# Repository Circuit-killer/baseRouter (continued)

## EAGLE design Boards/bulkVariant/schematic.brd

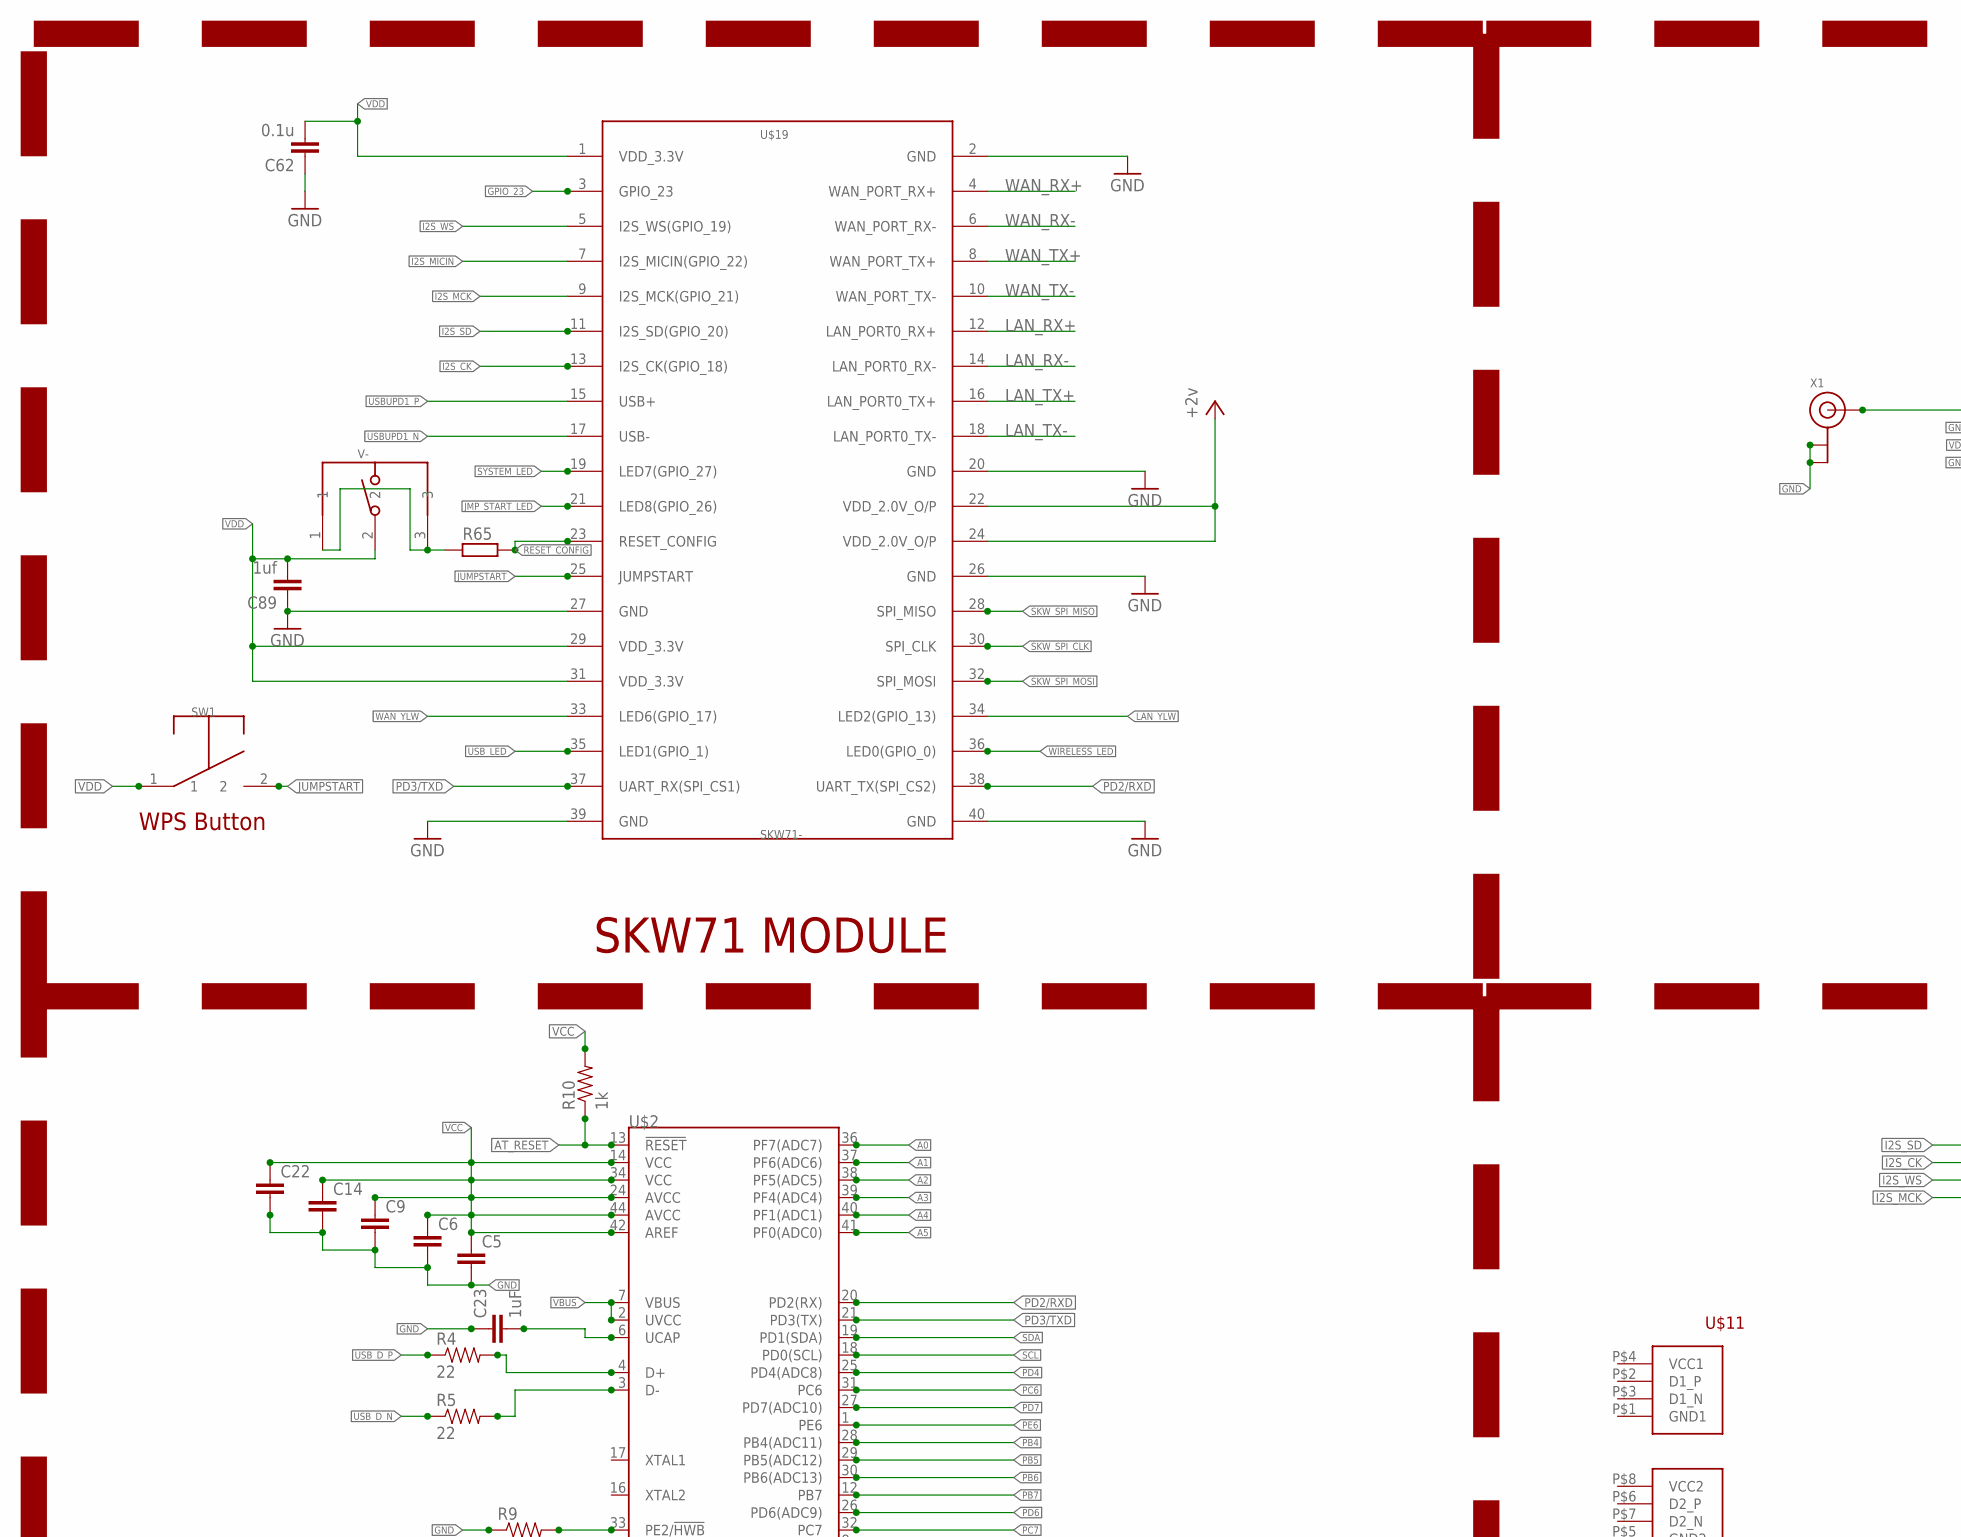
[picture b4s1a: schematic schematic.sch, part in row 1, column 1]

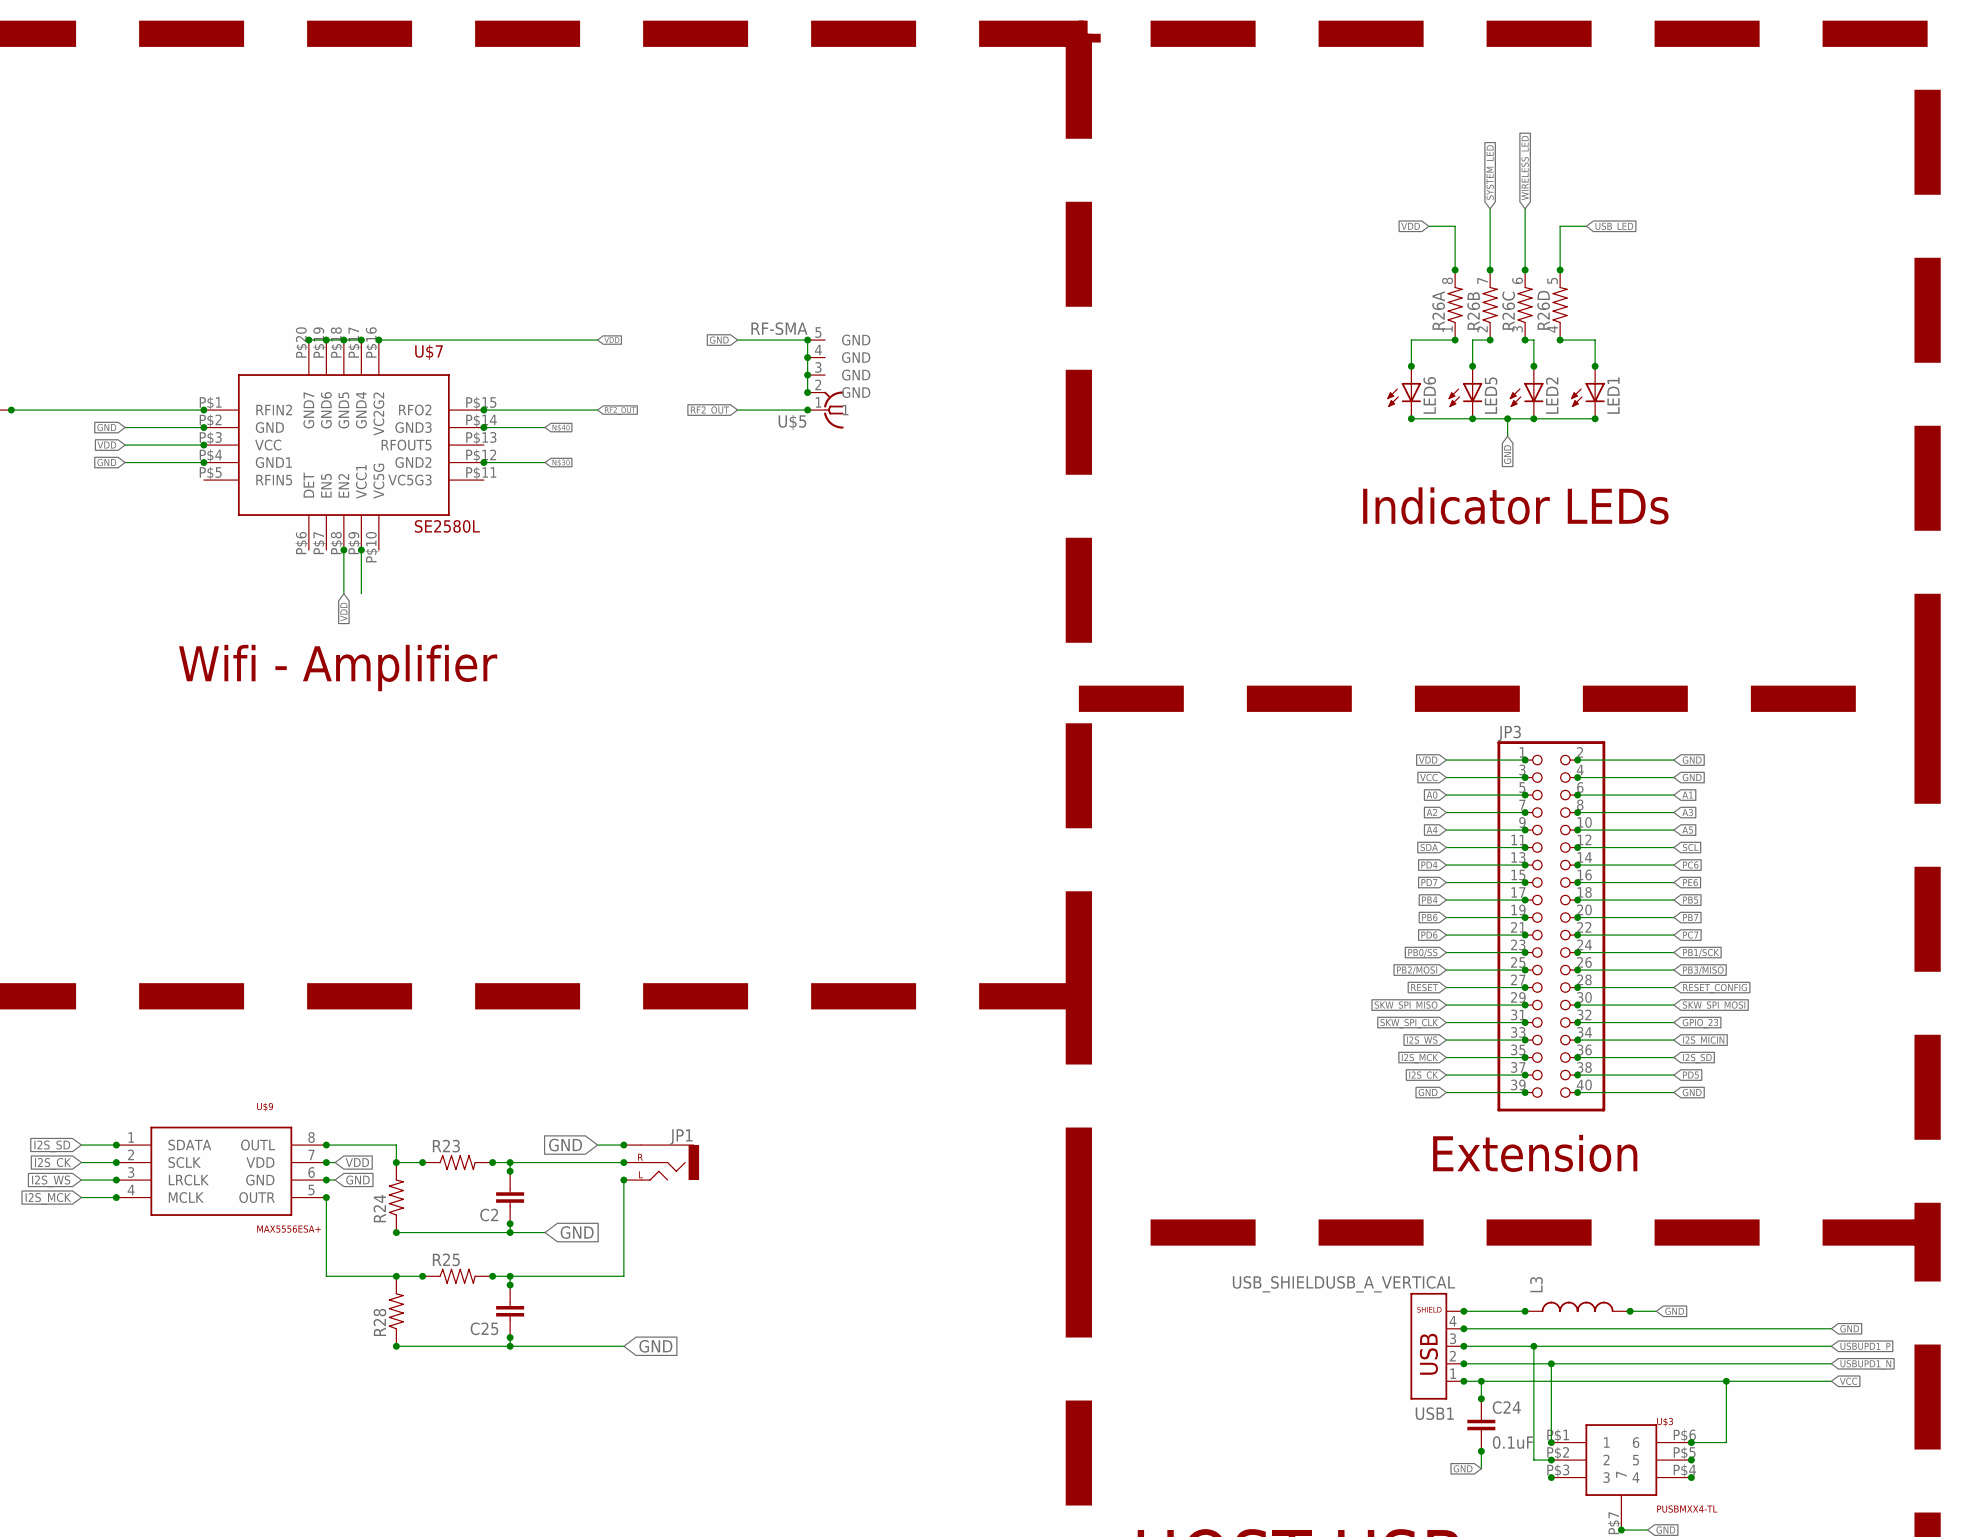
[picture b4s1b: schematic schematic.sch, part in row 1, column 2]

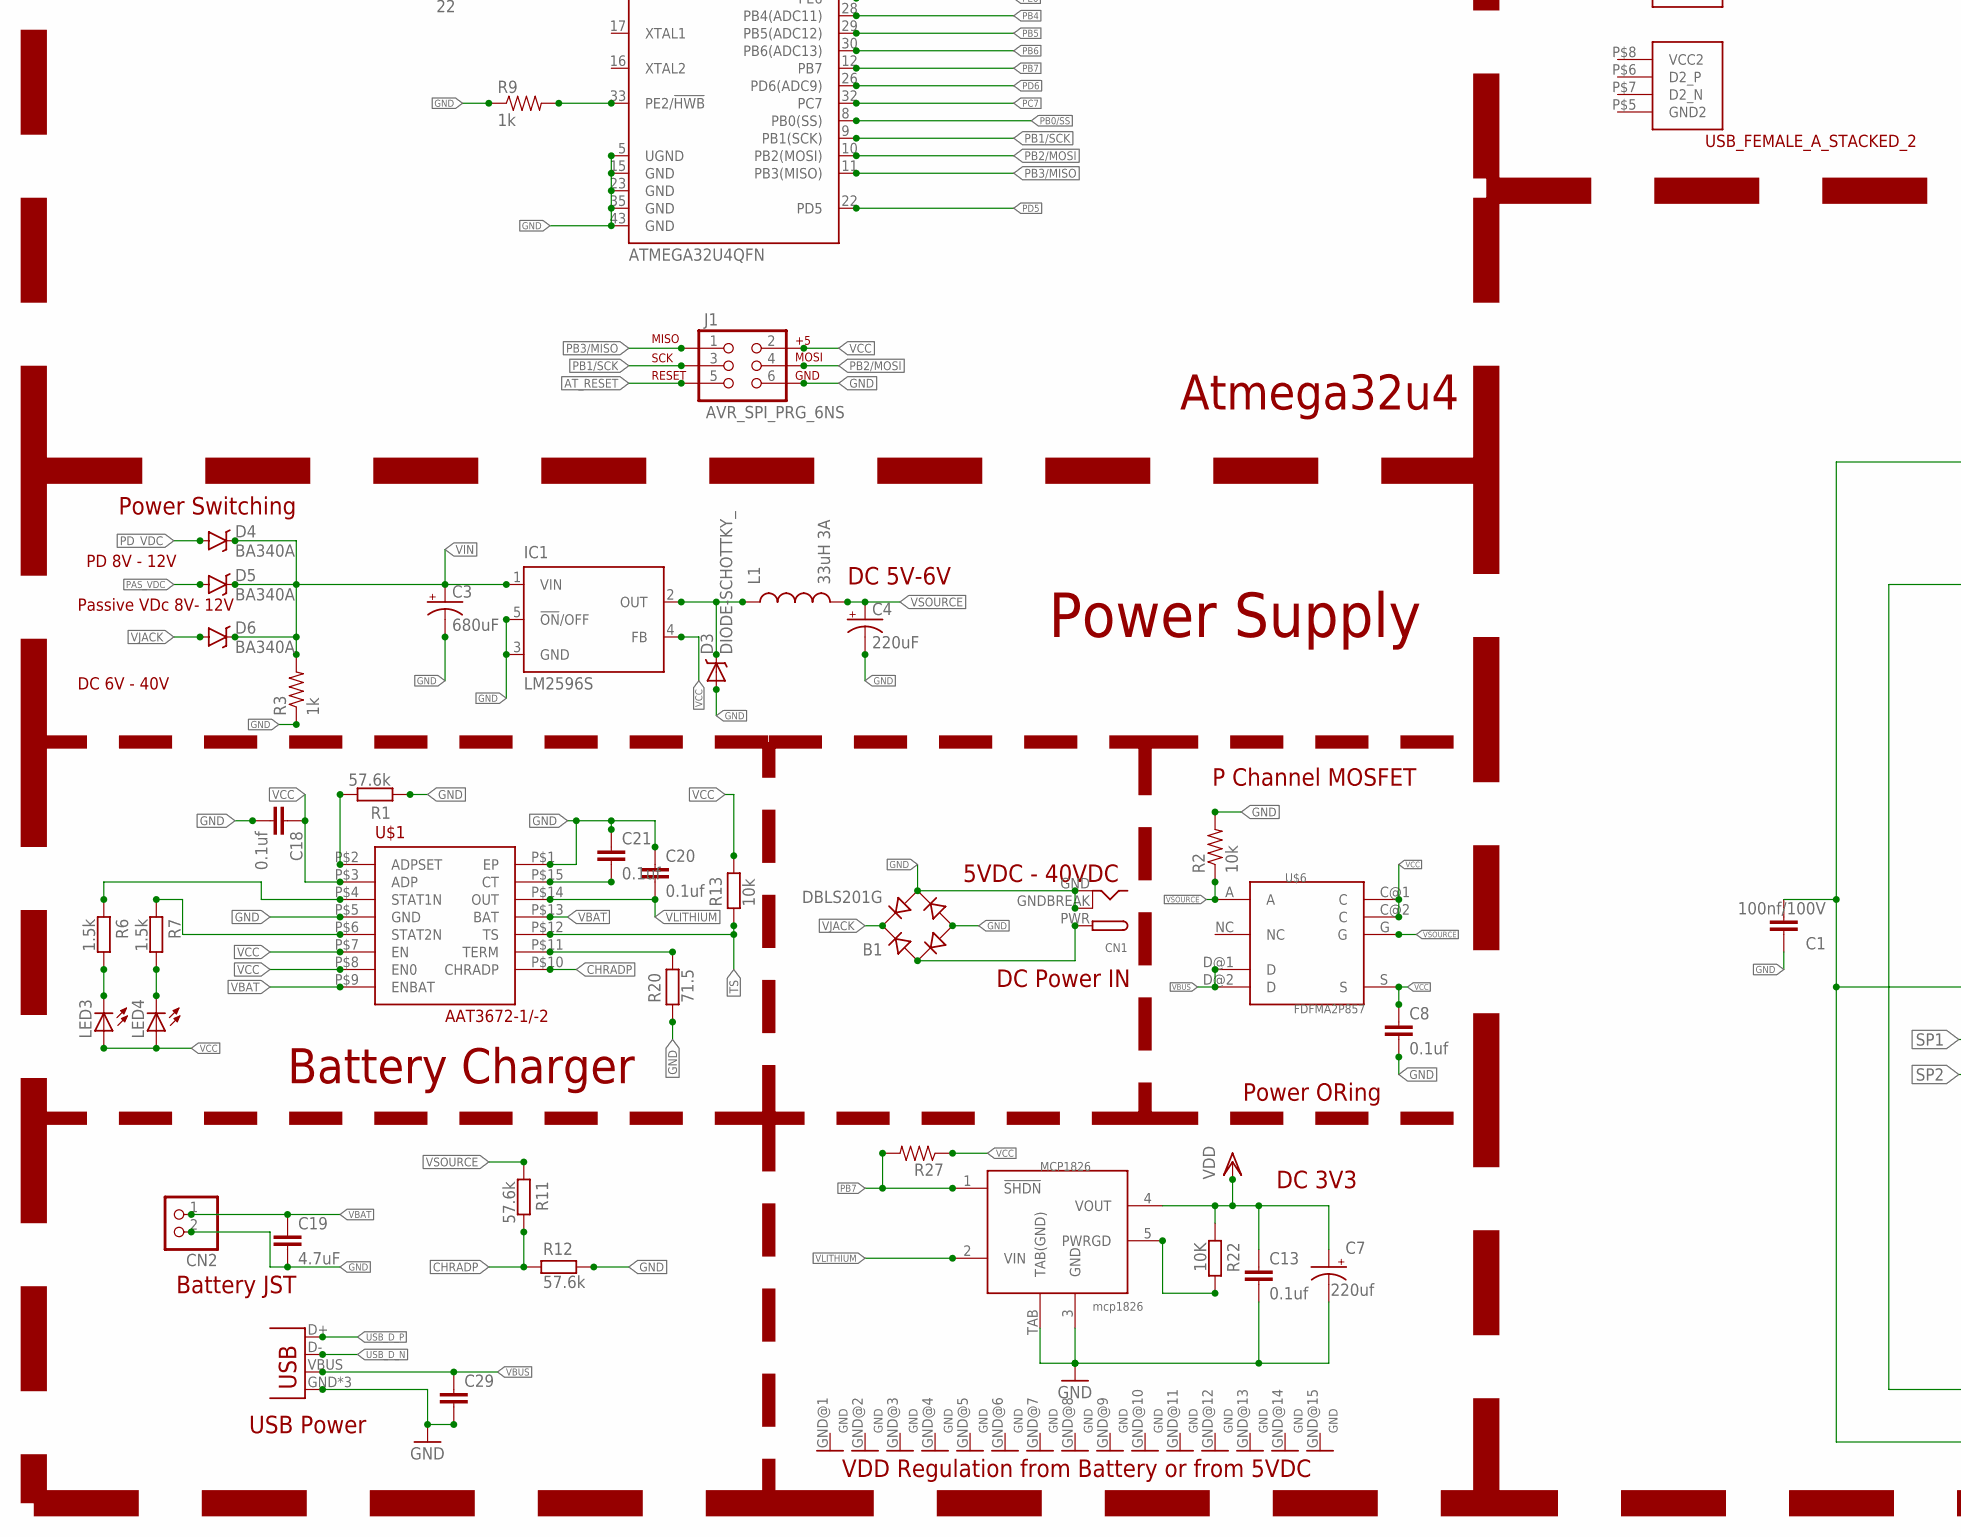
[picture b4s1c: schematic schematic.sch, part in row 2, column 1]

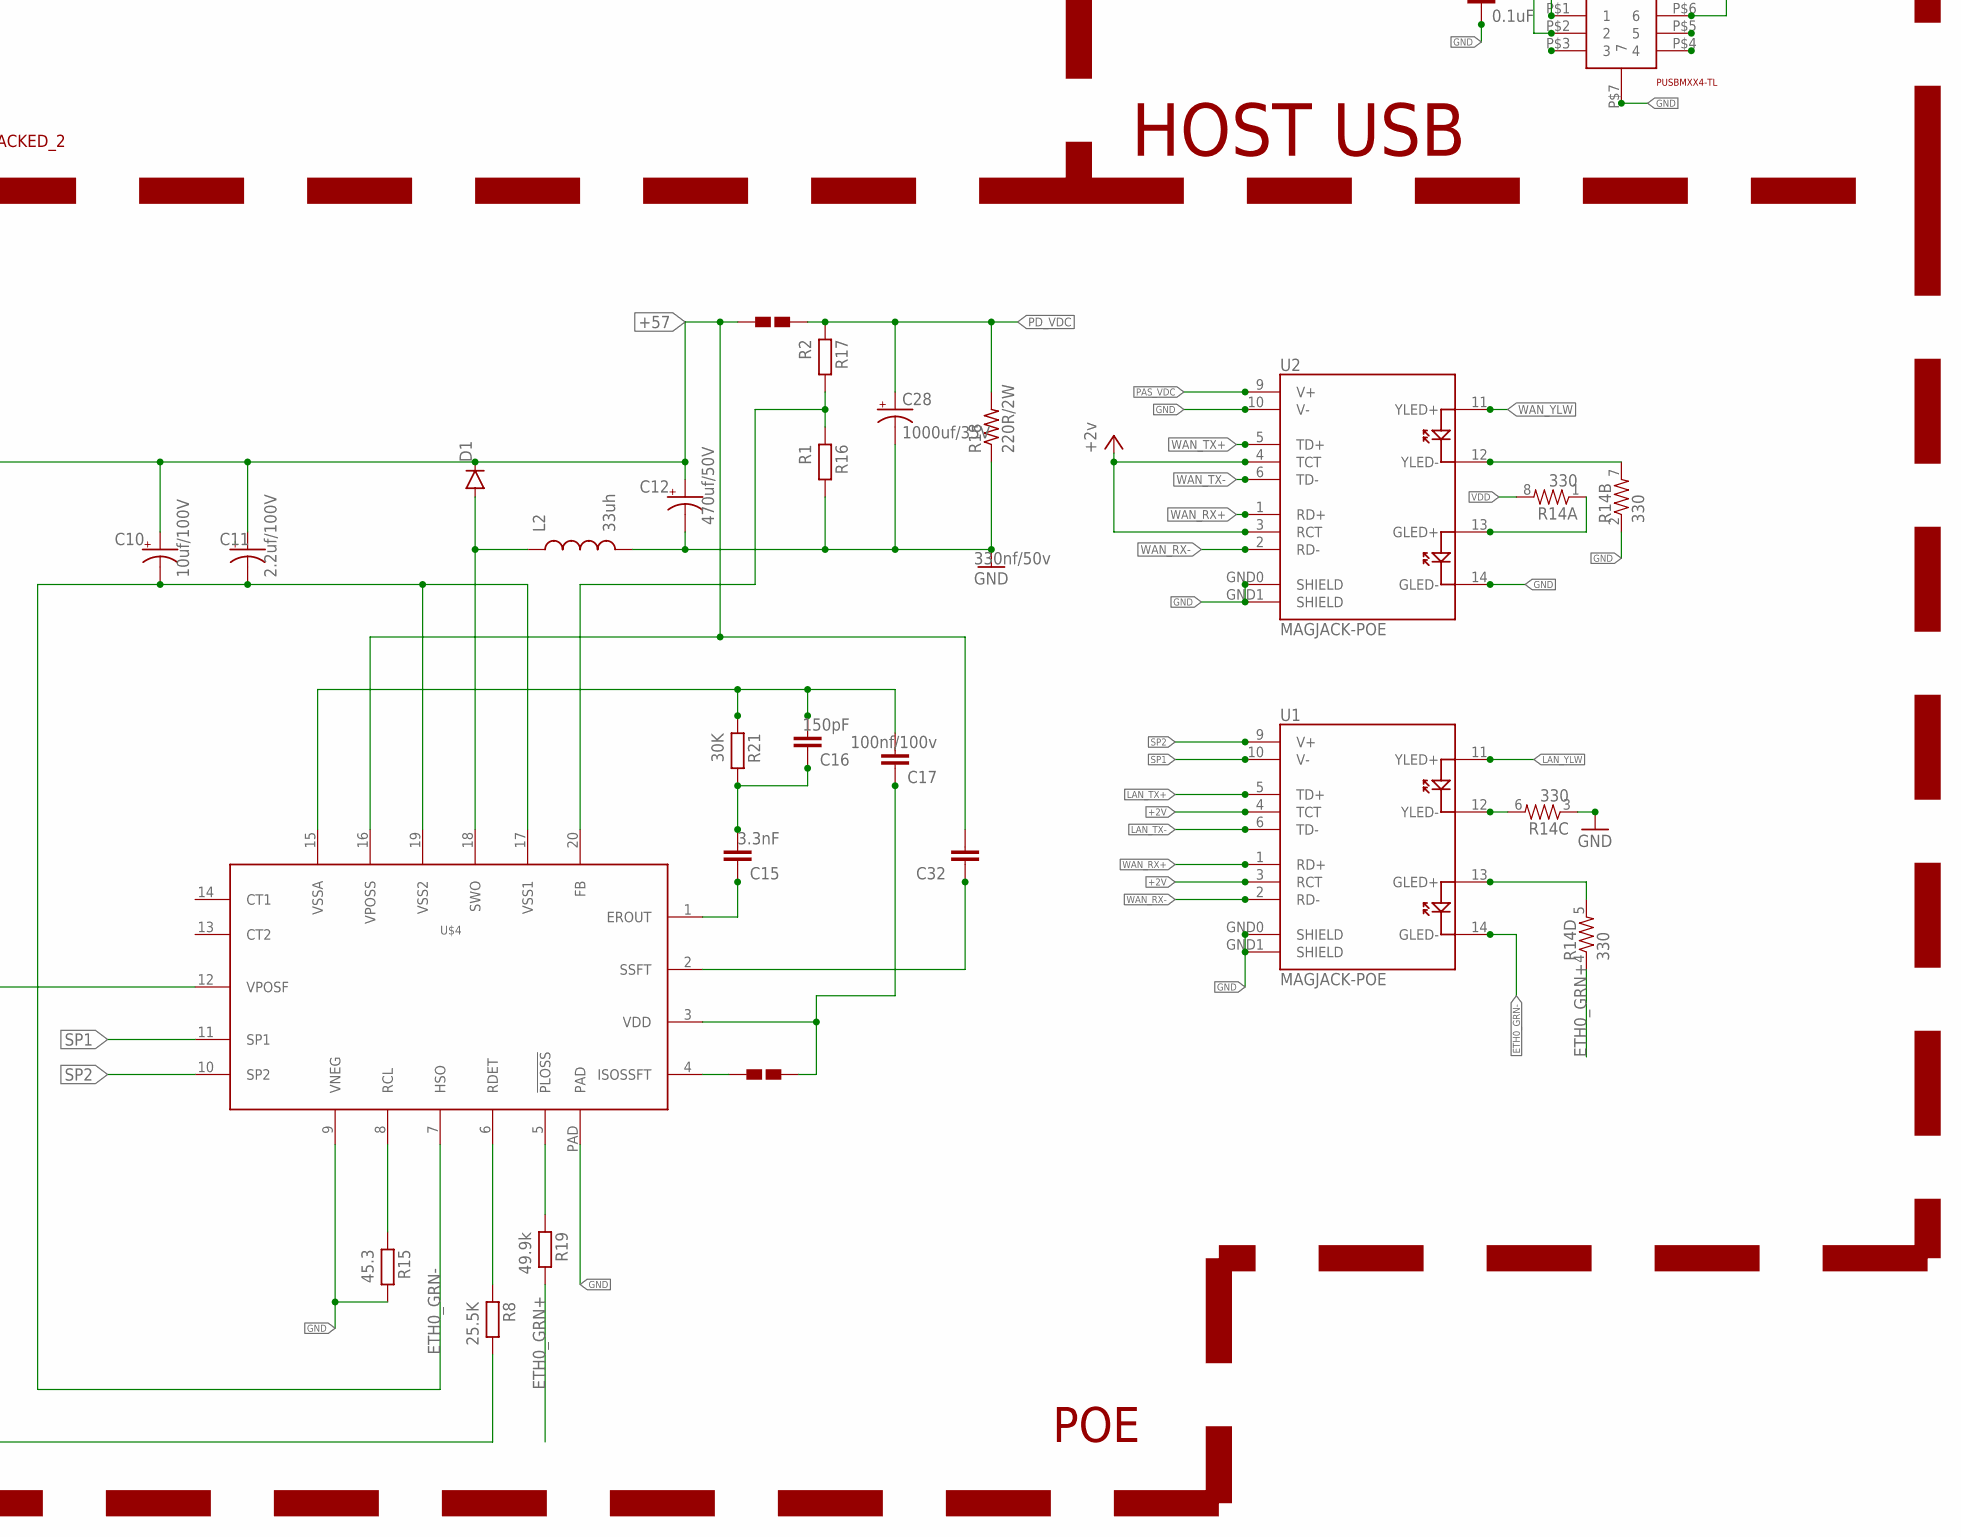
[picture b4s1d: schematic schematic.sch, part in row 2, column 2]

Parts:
B1: DBLS201G; DBS
C1: 100nf/100V; C0805
C2, C5, C6, C9, C14, C22, C25, C29: CAP0402-CAP; 0402-CAP
C3: 680uF; E3,5-10
C4: 220uF; E5-10,5
C7: 220uf; E5-10,5
C8, C13, C18, C20, C21: 0.1uf; C0603
C10: 10uf/100V; E2,5-6E
C11: 2.2uf/100V; E2-5
C12: 470uf/50V; E5-10,5
C15: 3.3nF; C0805
C16: 150pF; C0805
C17: 100nf/100v; C0805
C19: 4.7uF; C0603
C23: 1uF; 0402-CAP
C24: 0.1uF; 0402-CAP
C28: 1000uf/35V; E5-13
C32: 330nf/50v; C0805
C62: 0.1u; C0603
C89: 1uf; C0603
CN1: DCBARRELPTH; DCJACK_2MM_PTH
CN2: JST_2PIN-THM; JST-PH-2-THM
D1: DIODESMC/DO-214AB; SMC
D3: DIODE-SCHOTTKY_; SMA-DIODE
D4, D5, D6: BA340A; SMA-DIODE
IC1: LM2596S; TO263-5
J1: AVR_SPI_PRG_6NS; 2X3-NS
JP1: AUDIO-JACKSMD2; AUDIO-JACK-3.5MM-SMD
JP3: PINHD-2X20; 2X20
JP4: USB-MICROB
L1: 33uH 3A; INDUCTOR-10X9.8X6
L2: 33uh; INDUCTOR-10X9.8X6
L3: INDUCTOR0402; C0402
LED1, LED2, LED5, LED6: LED3MM
LED3, LED4: LEDCHIP-LED0603; CHIP-LED0603
MCP1826: mcp1826; SOT223-5
R1, R11, R12: 57.6k; R0402
R2: 10k; 0402-RES
R3, R9, R10: 1k; 0402-RES
R4, R5: 22; 0402-RES
R6, R7: 1.5k; R0402
R8: 25.5K; R0603
R13: 10k; R0402
R14: 330; 0603-ARV
R15: 45.3; R0603
R16: R1; R0603
R17: R2; R0603
R18: 220R/2W; R2512
R19: 49.9k; R0603
R20: 71.5; R0402
R21: 30K; R0603
R22: 10K; R0603
R23, R24, R25, R27, R28: RESISTOR0402-RES; 0402-RES
R26: RESISTOR-ARRAY0603-ARV; 0603-ARV
R65: RESISTOR; R0603
SW1: TACTILE-2PIN'; TACTILE-2PIN-RTANGLE
U1, U2: MAGJACK-POE
U$1: AAT3672-1/-2
U$2: ATMEGA32U4QFN; QFN-44
U$3: PUSBMXX4-TL
U$4: SI3402
U$5: RF-SMA; BU-SMA-H
U$6: FDFMA2P857; 6-WDFN-EXPOSED-PAD
U$7: SE2580L
U$9: MAX5556ESA+; SO-8
U$10, U$28: SOL-PAD-OPEN
U$11: USB_FEMALE_A_STACKED_2; USB_A_FEMALE_STACKED_2
U$19: SKW71-; SKW71-SMT
USB1: USB_SHIELDUSB_A_VERTICAL; USB_A_VERTICAL_PTH
V-: SPST-3PIN-RTANGLEP02; TL3340AF160QG
X1: ANTENNA_U.FL; U.FL

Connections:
+2V: U1.3 (RCT), U1.4 (TCT), U2.3 (RCT), U2.4 (TCT), U$19.22 (VDD_2.0V_O/P), U$19.24 (VDD_2.0V_O/P)
+57: C1.2, C10.+, C11.+, C12.+, C32.2, D1.C, R8.2, U$4.12 (VPOSF), U$4.16 (VPOSS), U$28.P$1 (1)
A0: JP3.5, U$2.36 (PF7(ADC7))
A1: JP3.6, U$2.37 (PF6(ADC6))
A2: JP3.7, U$2.38 (PF5(ADC5))
A3: JP3.8, U$2.39 (PF4(ADC4))
A4: JP3.9, U$2.40 (PF1(ADC1))
A5: JP3.10, U$2.41 (PF0(ADC0))
AT_RESET: J1.5, R10.1, U$2.13 (!RESET)
CHRADP: R11.2, R12.1, U$1.P$10 (CHRADP)
ETH0_GRN+: R14.4 (1), R19.2
ETH0_GRN-: C10.-, C11.-, U1.14 (GLED-), U$4.7 (HSO), U$4.17 (VSS1), U$4.19 (VSS2)
GND: B1.-, B1.AC2, C1.1, C2.1, C3.-, C4.-, C5.2, C6.2, C7.-, C8.2, C9.2, C12.-, C13.2, C14.2, C18.2, C19.2, C20.1, C21.1, C22.2, C23.1, C24.2, C25.1, C28.-, C29.2, C62.1, C89.1, CN1.GND, CN1.GNDBREAK, CN2.2 (1), D3.A, IC1.3 (GND), IC1.5 (!ON!/OFF), J1.6, JP1.SLEEVE, JP3.2, JP3.4, JP3.39, JP3.40, JP4.GND, JP4.MT1 (GND), JP4.MT2 (GND), L2.P$2 (2), L3.2, LED1.K (C), LED2.K (C), LED5.K (C), LED6.K (C), MCP1826.3 (GND), MCP1826.GND@1 (GND), MCP1826.GND@2 (GND), MCP1826.GND@3 (GND), MCP1826.GND@4 (GND), MCP1826.GND@5 (GND), MCP1826.GND@6 (GND), MCP1826.GND@7 (GND), MCP1826.GND@8 (GND), MCP1826.GND@9 (GND), MCP1826.GND@10 (GND), MCP1826.GND@11 (GND), MCP1826.GND@12 (GND), MCP1826.GND@13 (GND), MCP1826.GND@14 (GND), MCP1826.GND@15 (GND), MCP1826.TAB (TAB(GND)), R1.1, R2.2, R3.1, R9.1, R12.2, R14.2 (1), R14.3 (1), R15.2, R16.2, R18.1, R20.1, R24.1, R28.1, U1.GND0 (SHIELD), U1.GND1 (SHIELD), U2.10 (V-), U2.14 (GLED-), U2.GND0 (SHIELD), U2.GND1 (SHIELD), U$1.P$1 (EP), U$1.P$5 (GND), U$2.5 (UGND), U$2.15 (GND), U$2.23 (GND), U$2.35 (GND), U$2.43 (GND), U$3.P$7 (7), U$4.9 (VNEG), U$4.PAD, U$5.2 (GND), U$5.3 (GND), U$5.4 (GND), U$5.5 (GND), U$7.P$2 (GND), U$7.P$4 (GND1), U$9.6 (GND), U$19.2 (GND), U$19.20 (GND), U$19.26 (GND), U$19.27 (GND), U$19.39 (GND), U$19.40 (GND), USB1.4, X1.1 (GND), X1.2 (GND)
GPIO_23: JP3.32, U$19.3 (GPIO_23)
I2S_CK: JP3.37, U$9.2 (SCLK), U$19.13 (I2S_CK(GPIO_18))
I2S_MCK: JP3.35, U$9.4 (MCLK), U$19.9 (I2S_MCK(GPIO_21))
I2S_MICIN: JP3.34, U$19.7 (I2S_MICIN(GPIO_22))
I2S_SD: JP3.36, U$9.1 (SDATA), U$19.11 (I2S_SD(GPIO_20))
I2S_WS: JP3.33, U$9.3 (LRCLK), U$19.5 (I2S_WS(GPIO_19))
JMP_START_LED: U$19.21 (LED8(GPIO_26))
JUMPSTART: SW1.2, U$19.25 (JUMPSTART)
LAN_RX+: U$19.12 (LAN_PORT0_RX+)
LAN_RX-: U$19.14 (LAN_PORT0_RX-)
LAN_TX+: U1.5 (TD+), U$19.16 (LAN_PORT0_TX+)
LAN_TX-: U1.6 (TD-), U$19.18 (LAN_PORT0_TX-)
LAN_YLW: U1.11 (YLED+), U$19.34 (LED2(GPIO_13))
unnamed: D3.C, IC1.2 (OUT), L1.P$1 (1)
unnamed: R1.2, U$1.P$2 (ADPSET)
unnamed: C16.2, C17.2, R21.1, U$4.15 (VSSA)
unnamed: C15.2, C16.1, R21.2
unnamed: R8.1, U$4.6 (RDET)
unnamed: R15.1, U$4.8 (RCL)
unnamed: D1.A, L2.P$1 (1), U$4.18 (SWO)
unnamed: U$4.4 (ISOSSFT), U$10.P$1 (1)
unnamed: C17.1, U$4.3 (VDD), U$10.P$2 (2)
unnamed: C15.1, U$4.1 (EROUT)
unnamed: R23.1, R24.2, U$9.8 (OUTL)
unnamed: C32.1, U$4.2 (SSFT)
unnamed: R16.1, R17.2, U$4.20 (FB)
unnamed: R19.1, U$4.5 (!PLOSS)
unnamed: U$7.P$17 (GND4), U$7.P$18 (GND5), U$7.P$19 (GND6), U$7.P$20 (GND7)
unnamed: MCP1826.5 (PWRGD), R22.2
unnamed: R6.1, U$1.P$4 (STAT1N)
unnamed: R14.6 (2), U1.12 (YLED-)
unnamed: R14.1, U2.13 (GLED+)
unnamed: R65.1, V-.1, V-.3
unnamed: R25.1, R28.2, U$9.5 (OUTR)
unnamed: R7.1, U$1.P$6 (STAT2N)
unnamed: R14.7 (2), U2.12 (YLED-)
unnamed: R20.2, U$1.P$11 (TERM)
unnamed: C23.2, U$2.6 (UCAP)
unnamed: R4.2, U$2.4 (D+)
unnamed: R5.2, U$2.3 (D-)
unnamed: L3.1, USB1.P$3 (5)
unnamed: C21.2, U$1.P$15 (CT)
unnamed: R9.2, U$2.33 (PE2/!HWB)
unnamed: B1.AC1, CN1.PWR
unnamed: LED6.A, R26.1
unnamed: LED5.A, R26.2 (1)
unnamed: LED4.C, R7.2
unnamed: LED3.C, R6.2
unnamed: LED2.A, R26.3 (1)
unnamed: LED1.A, R26.4 (1)
unnamed: U$7.P$1 (RFIN2), X1.3 (SIGNAL)
unnamed: C2.2, JP1.RING (RIGHT), R23.2
unnamed: C25.2, JP1.TIP (LEFT), R25.2
unnamed: R14.5 (2), U1.13 (GLED+)
PAS_VDC: D5.A, U2.9 (V+)
PB0/SS: JP3.23, U$2.8 (PB0(SS))
PB1/SCK: J1.3, JP3.24, U$2.9 (PB1(SCK))
PB2/MOSI: J1.4, JP3.25, U$2.10 (PB2(MOSI))
PB3/MISO: J1.1, JP3.26, U$2.11 (PB3(MISO))
PB4: JP3.17, U$2.28 (PB4(ADC11))
PB5: JP3.18, U$2.29 (PB5(ADC12))
PB6: JP3.19, U$2.30 (PB6(ADC13))
PB7: JP3.20, MCP1826.1 (!SHDN), R27.2, U$2.12 (PB7)
PC6: JP3.14, U$2.31 (PC6)
PC7: JP3.22, U$2.32 (PC7)
PD2/RXD: U$2.20 (PD2(RX)), U$19.38 (UART_TX(SPI_CS2))
PD3/TXD: U$2.21 (PD3(TX)), U$19.37 (UART_RX(SPI_CS1))
PD4: JP3.13, U$2.25 (PD4(ADC8))
PD5: JP3.38, U$2.22 (PD5)
PD6: JP3.21, U$2.26 (PD6(ADC9))
PD7: JP3.15, U$2.27 (PD7(ADC10))
PD_VDC: C28.+, D4.A, R17.1, R18.2, U$28.P$2 (2)
PE6: JP3.16, U$2.1 (PE6)
RESET: JP3.27
RESET_CONFIG: JP3.28, R65.2, U$19.23 (RESET_CONFIG)
RF2_OUT: U$5.1, U$7.P$15 (RFO2)
SCL: JP3.12, U$2.18 (PD0(SCL))
SDA: JP3.11, U$2.19 (PD1(SDA))
SKW_SPI_CLK: JP3.31, U$19.30 (SPI_CLK)
SKW_SPI_MISO: JP3.29, U$19.28 (SPI_MISO)
SKW_SPI_MOSI: JP3.30, U$19.32 (SPI_MOSI)
SP1: U1.10 (V-), U$4.11 (SP1)
SP2: U1.9 (V+), U$4.10 (SP2)
SYSTEM_LED: R26.7 (2), U$19.19 (LED7(GPIO_27))
TS: R13.1, U$1.P$12 (TS)
USBUPD1_N: U$3.P$1 (1), U$19.17 (USB-), USB1.2
USBUPD1_P: U$3.P$2 (2), U$19.15 (USB+), USB1.3
USB_D_N: JP4.D-, R5.1
USB_D_P: JP4.D+, R4.1
USB_LED: R26.5 (2), U$19.35 (LED1(GPIO_1))
VBAT: C19.1, CN2.1 (2), U$1.P$9 (ENBAT), U$1.P$13 (BAT)
VBUS: C29.1, JP4.VBUS, U$2.2 (UVCC), U$2.7 (VBUS), U$6.D@1 (D), U$6.D@2 (D)
VCC: C5.1, C6.1, C8.1, C9.1, C14.1, C18.1, C22.1, C24.1, IC1.4 (FB), J1.2, JP3.3, LED3.A, LED4.A, R10.2, R13.2, R27.1, U$1.P$3 (ADP), U$1.P$7 (EN), U$1.P$8 (EN0), U$2.14 (VCC), U$2.24 (AVCC), U$2.34 (VCC), U$2.42 (AREF), U$2.44 (AVCC), U$3.P$6 (6), U$6.C@1 (C), U$6.C@2 (C), U$6.S, USB1.1
VDD: C7.+, C13.1, C62.2, C89.2, JP3.1, MCP1826.4 (VOUT), R14.8 (2), R22.1, R26.8 (2), SW1.1, U$7.P$3 (VCC), U$7.P$8 (EN2), U$7.P$16 (VC2G2), U$9.7 (VDD), U$19.1 (VDD_3.3V), U$19.29 (VDD_3.3V), U$19.31 (VDD_3.3V), V-.2
VIN: C3.+, D4.C, D5.C, D6.C, IC1.1 (VIN), R3.2
VJACK: B1.+, D6.A
VLITHIUM: C20.2, MCP1826.2 (VIN), U$1.P$14 (OUT)
VSOURCE: C4.+, L1.P$2 (2), R2.1, R11.1, U$6.A, U$6.G
WAN_RX+: U1.1 (RD+), U2.1 (RD+), U$19.4 (WAN_PORT_RX+)
WAN_RX-: U1.2 (RD-), U2.2 (RD-), U$19.6 (WAN_PORT_RX-)
WAN_TX+: U2.5 (TD+), U$19.8 (WAN_PORT_TX+)
WAN_TX-: U2.6 (TD-), U$19.10 (WAN_PORT_TX-)
WAN_YLW: U$19.33 (LED6(GPIO_17))
WIRELESS_LED: R26.6 (2), U$19.36 (LED0(GPIO_0))

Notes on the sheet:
POE
SKW71 MODULE
5VDC - 40VDC
PD 8V - 12V
Passive VDc 8V- 12V
Power Switching
USB Power
Battery JST
VDD Regulation from Battery or from 5VDC
DC Power IN
Power Supply
DC 5V-6V
DC 6V - 40V
DC 3V3
Power ORing
P Channel MOSFET
HOST USB
Extension
Battery Charger
Atmega32u4
WPS Button
Wifi - Amplifier
Indicator LEDs

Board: 2 copper layers, 100 parts (14 on the bottom side), 112 nets, no tracks yet.

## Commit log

2014-09-12 Initial Commit.
2014-09-12 untitled file removed.
2014-09-12 intial commits of files.
2014-09-13 Development in supply section, ongoing...
2014-09-14 Schematic Reframed.
2014-09-15 Normal Push
2014-09-15 normal Push.
2014-09-18 Normal Push, With Surge Protection on Host USB.
2014-09-18 Removing duplicate file from here.l
2014-09-25 Normal Push Signed-off-by: pixma38@gmail.com <pixma38@gmail.com>
2014-10-14 cleanin deleted stuff here.
2014-12-08 cad file added, enclosure rev B progressed, live now. bttom done.
2014-12-09 top part_build.
2015-04-22 Closure commit
2015-04-22 Readme updated
